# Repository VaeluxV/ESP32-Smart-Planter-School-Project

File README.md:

# ESP32 Smart Planter
## Hardware info
### Required Hardware:
* ESP32 Devkit (30-pins)
* Soil moisture sensor
* PN532 rfid reader
* Passive buzzer
* LDR
* Ds18b20 Soil temperature sensor
* Water Level Sensor
* Bme280
* 5V 4-channel relay module (a 2-channel module can also be used if you do not plan to add more hardware yourself)
* I2C LCD (min. 4 lines, 20 characters per line)
* Wire
### Optional hardware:
* Custom PCB (gerber files can be found under [`/CustomPCB/Gerber`](https://github.com/VaeluxV/ESP32-Smart-Planter-School-Project/tree/main/CustomPCB/Gerber) and eagle schematics under [`/Eagle/ESP-Planter`](https://github.com/VaeluxV/ESP32-Smart-Planter-School-Project/tree/main/Eagle/ESP-Planter))

## Software info

### Required software:
* Arduino IDE or VS Code (Platformio) (originally developed for/using Platformio)

### Required libraries:
* SPI
* Adafruit_PN532
* Wire
* LiquidCrystal_I2C
* Adafruit_Sensor
* Adafruit_BME280
* FastLED
* OneWire
* DallasTemperature
* WiFi
* PubSubClient
* freertos/FreeRTOS
* freertos/task

### The code:
You can find the code for the ESP32 under [`/src/main.cpp`](https://github.com/VaeluxV/ESP32-Smart-Planter-School-Project/blob/main/src/main.cpp)

---

## Other info

This project works using Grafana, InfluxDB & MQTT installed on any device such as a Raspberry Pi. You can remove the Grafana & InfluxDB if you do not need to store any data but it is not recommended because I have not tested the full functionality without these programs. MQTT is required if you do not modify any code.

Make sure to enter your WiFi and MQTT details when uploading this code to your ESP32 or it won't work!

MQTT settings can be found at line 18-21 and WiFi settings can be found at line 32-33.
Other configurable settings can also be found near the top of the code. This can be used if your LCD has a different I2C adress (line 44) for example.

The InfluxDB connection requires a database names `planter_readings` to be present so make sure to make that before starting the MQTT bridge!

Connections schematic (default config):

Please note that the 12v & 5v connections are external connections coming from a 12v PSU (& buck converter for the 5v) while the 3.3v is delivered by the ESP32's internal power conversion.

---

### Relays and 12v components
The 5v relay module, 12v fan & 12v water pump are not shown in this schematic but have to be connected too. The fan is connected to relay channel 1, while the pump is connected on channel 2. All of these share a common ground with the esp32 (through the buck converter).

### Debugging connection
Debugging can be done over serial (9600 baud) using the USB connection. Make sure to still plug in the PSU as otherwise there will not be enough power to run everything and the ESP32 will possibly fail to boot properly!

---

You are free to open issues if you have any questions about something not documented here or otherwise not mentioned.

GLHF!

~ Vaelux

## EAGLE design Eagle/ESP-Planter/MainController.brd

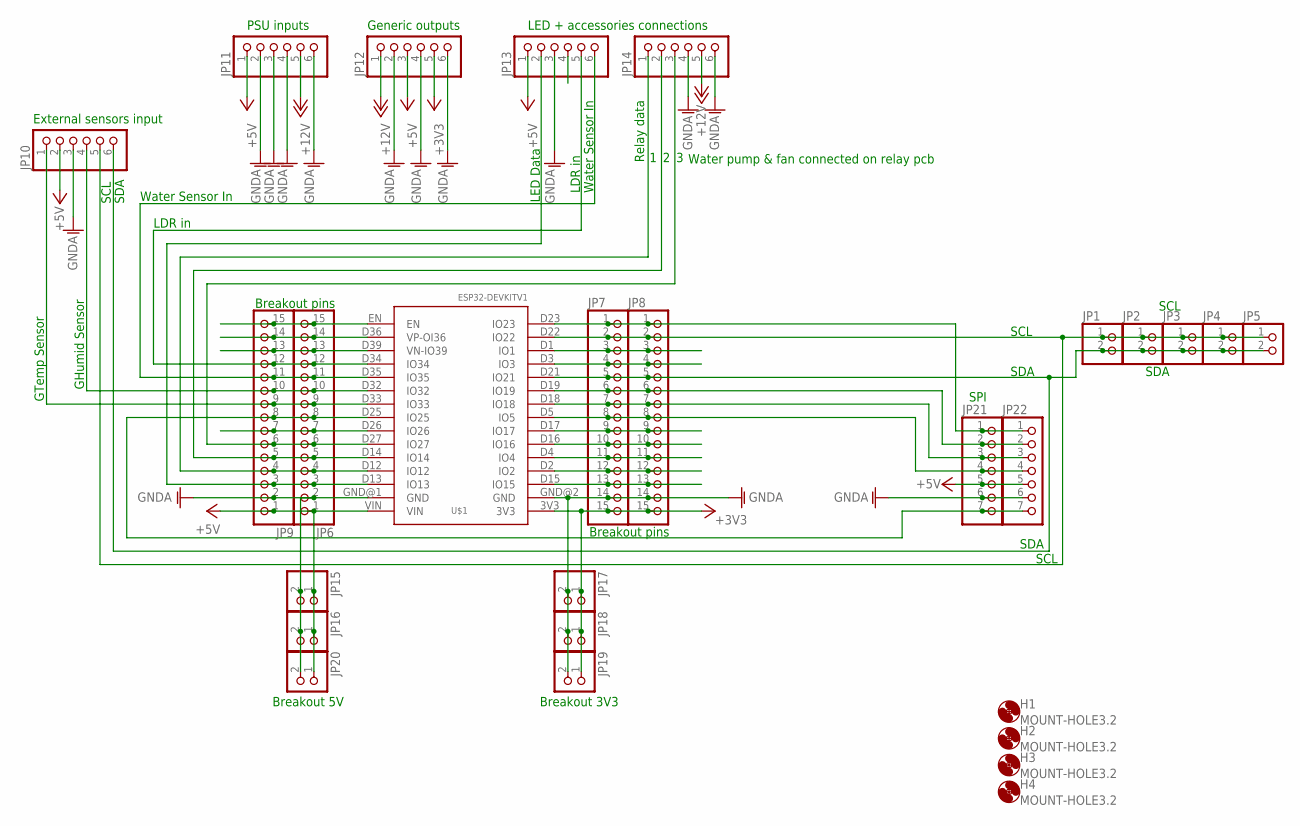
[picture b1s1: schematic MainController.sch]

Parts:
H1, H2, H3, H4: MOUNT-HOLE3.2; 3,2
JP1, JP2, JP3, JP4, JP5, JP15, JP16, JP17, JP18, JP19, JP20: PINHD-1X2; 1X02
JP6, JP7, JP8, JP9: PINHD-1X15; 1X15
JP10, JP11, JP12, JP13, JP14: PINHD-1X6; 1X06
JP21, JP22: PINHD-1X7; 1X07
U$1: ESP32DEVKITV1; ESP32-DEVKITV1

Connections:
+3V3: JP7.15, JP8.15, JP12.5, JP17.1, JP18.1, JP19.1, U$1.3V3
+5V: JP6.1, JP9.1, JP10.2, JP11.1, JP12.3, JP13.1, JP15.1, JP16.1, JP20.1, JP21.5, JP22.5, U$1.VIN
+12V: JP11.5, JP12.1, JP14.5
GNDA: JP6.2, JP7.14, JP8.14, JP9.2, JP10.3, JP11.2, JP11.3, JP11.4, JP11.6, JP12.2, JP12.4, JP12.6, JP13.3, JP14.4, JP14.6, JP15.2, JP16.2, JP17.2, JP18.2, JP19.2, JP20.2, JP21.6, JP22.6, U$1.GND@1 (GND), U$1.GND@2 (GND)
unnamed: JP6.10, JP9.10, JP10.4, U$1.D32 (IO32)
unnamed: JP6.9, JP9.9, JP10.1, U$1.D33 (IO33)
unnamed: JP7.9, JP8.9, U$1.D17 (IO17)
unnamed: JP6.7, JP9.7, U$1.D26 (IO26)
unnamed: JP7.6, JP8.6, JP21.2, JP22.2, U$1.D19 (IO19)
unnamed: JP7.1, JP8.1, JP21.1, JP22.1, U$1.D23 (IO23)
unnamed: JP6.13, JP9.13, U$1.D39 (VN-IO39)
unnamed: JP6.14, JP9.14, U$1.D36 (VP-OI36)
unnamed: JP6.15, JP9.15, U$1.EN
unnamed: JP1.1, JP2.1, JP3.1, JP4.1, JP5.1, JP7.2, JP8.2, JP10.5, U$1.D22 (IO22)
unnamed: JP6.3, JP9.3, JP13.2, U$1.D13 (IO13)
unnamed: JP6.12, JP9.12, JP13.5, U$1.D34 (IO34)
unnamed: JP7.3, JP8.3, U$1.D1 (IO1)
unnamed: JP7.4, JP8.4, U$1.D3 (IO3)
unnamed: JP1.2, JP2.2, JP3.2, JP4.2, JP5.2, JP7.5, JP8.5, JP10.6, U$1.D21 (IO21)
unnamed: JP6.4, JP9.4, JP14.1, U$1.D12 (IO12)
unnamed: JP6.5, JP9.5, JP14.2, U$1.D14 (IO14)
unnamed: JP7.8, JP8.8, JP21.4, JP22.4, U$1.D5 (IO5)
unnamed: JP7.10, JP8.10, U$1.D16 (IO16)
unnamed: JP7.11, JP8.11, U$1.D4 (IO4)
unnamed: JP7.12, JP8.12, U$1.D2 (IO2)
unnamed: JP7.13, JP8.13, U$1.D15 (IO15)
unnamed: JP6.11, JP9.11, JP13.6, U$1.D35 (IO35)
unnamed: JP6.8, JP9.8, JP21.7, JP22.7, U$1.D25 (IO25)
unnamed: JP7.7, JP8.7, JP21.3, JP22.3, U$1.D18 (IO18)
unnamed: JP6.6, JP9.6, JP14.3, U$1.D27 (IO27)

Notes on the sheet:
PSU inputs
Generic outputs
LED + accessories connections
LED Data
Relay data
External sensors input
SDA
SCL
GTemp Sensor
GHumid Sensor
Water Sensor In
Breakout pins
LDR in
Water pump & fan connected on relay pcb
Breakout 5V
Breakout 3V3
SPI

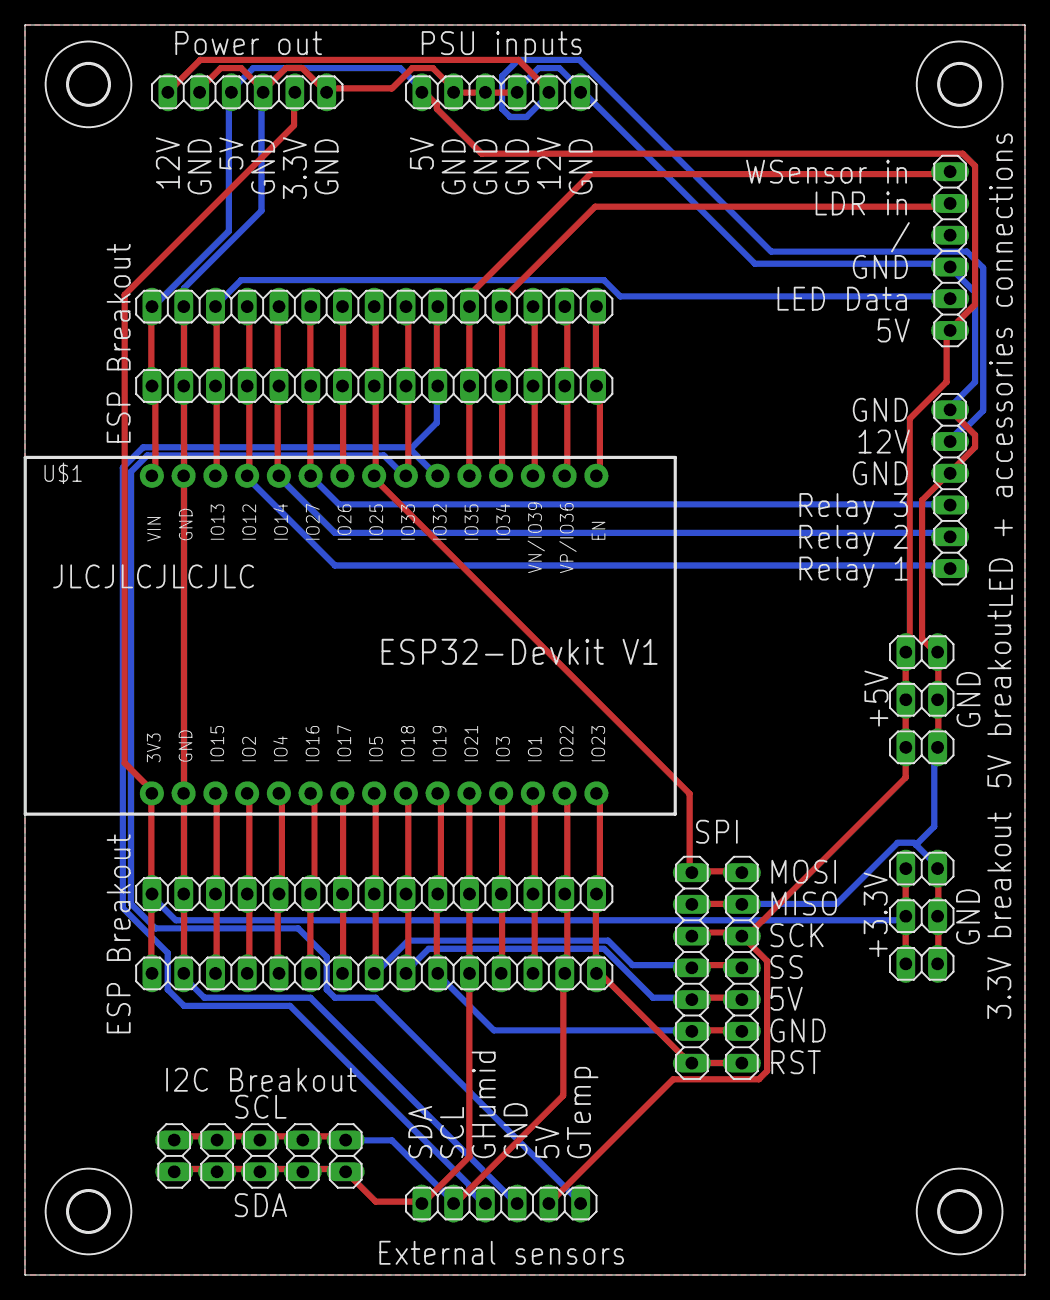
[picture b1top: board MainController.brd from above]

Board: 2 copper layers, 80.0 x 100.0 mm, 27 parts (0 on the bottom side), 30 nets.

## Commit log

2024-05-13 Added LCD
2024-05-13 Stuck on RFID read & added soil temp
2024-05-13 Working RFID + keeps track of plant type
2024-05-13 added LDR + leds
2024-05-14 added relay channels
2024-05-14 Add LCD task + delayed start of relay
2024-05-14 Add PCB + update documentation
2024-05-14 added eagle schematic
2024-05-28 tweaked variable names
2024-05-28 Add MQTT
2024-05-28 Add screenshots + tweaks
2024-05-29 tweaks
2024-06-09 Added water level sensor + manual water pump
2024-06-09 Add schematic picture
2024-06-11 Add pump status + fixed fan status
2024-06-11 Support fan & pump status properly
2024-06-11 Pump status displays/sends correctly
2024-06-11 Fix humidity reading being inverted
2024-06-11 Tweak
2024-06-11 Add more comments + update docs
2024-06-11 Update docs
2024-06-12 add pictures of Grafana
